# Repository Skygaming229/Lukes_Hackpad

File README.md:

Inspiration
- I wanted to create a macropad that allowed me to work more efficiently. I created a macropad using 6 switches, 1 rp2040, and 2 leds.

Challenges
- Believe it or not, this was my first time using Fusion 360 and KICad! I'm pretty proud of the final product. I had the most truble importing the PCB File into Fusion.

Specifications
BOM:

- 6x Cherry MX Switches
- 2x SK6812 MINI Leds
- 1x XIAO RP2040
- 4x Blank DSA Keycaps
- 4x M3x16 Bolt
- 4x M3 Heatset

Others:

- KMK Firmware
- Heckerpad_luke_case.stl
- Top_Heckpad_Luke.stl

Schematic            |  PCB         |   Case
:-------------------------:|:-------------------------:|:------------------------------:
    |    |

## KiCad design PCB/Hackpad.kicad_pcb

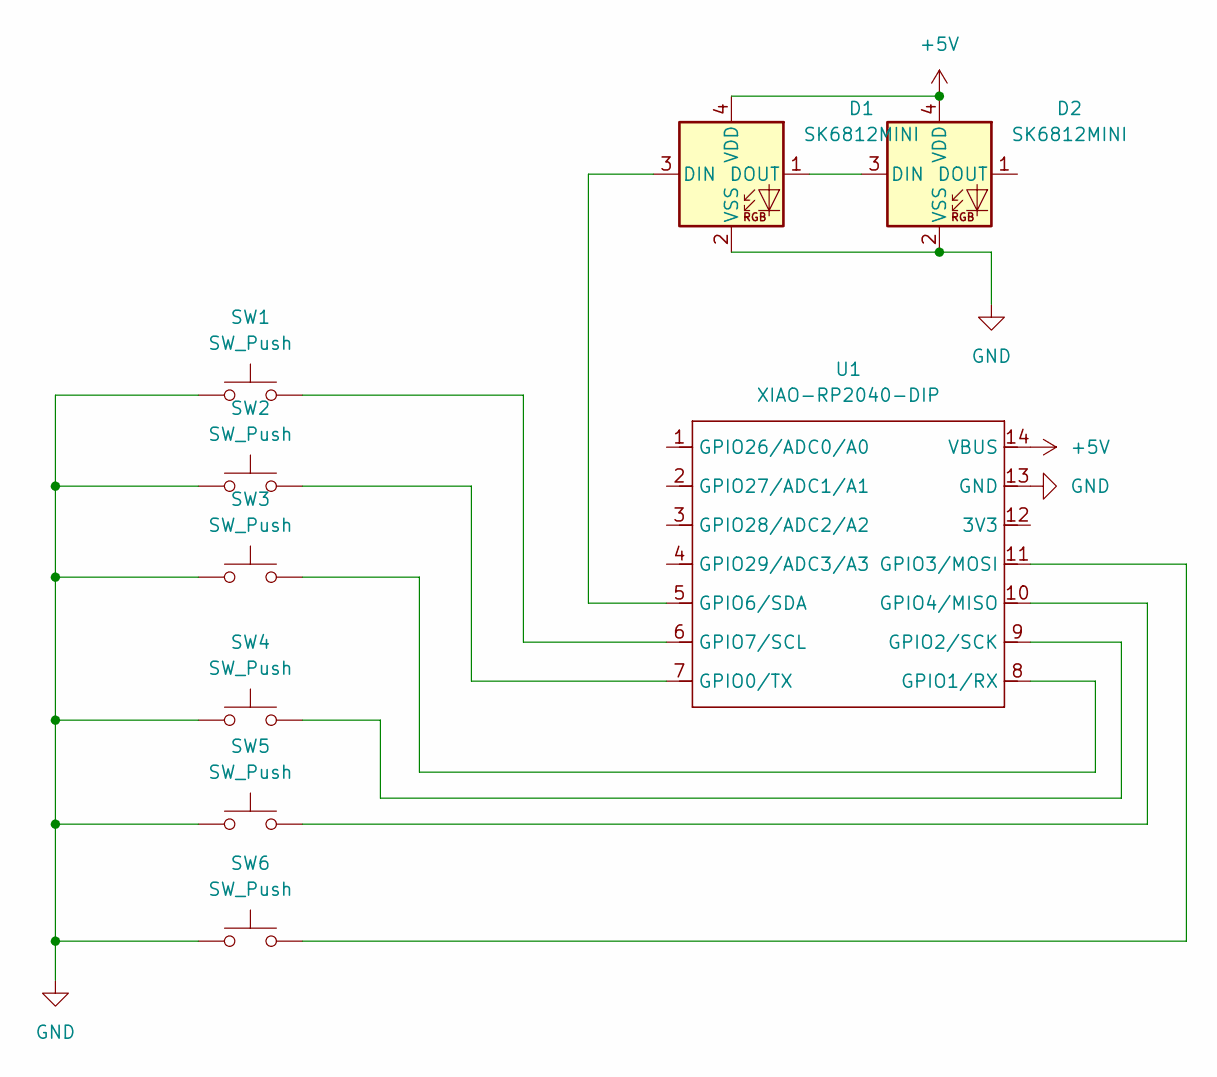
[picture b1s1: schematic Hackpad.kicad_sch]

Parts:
D1, D2: SK6812MINI; LED_SK6812MINI_PLCC4_3.5x3.5mm_P1.75mm
SW1, SW2, SW3, SW4, SW5, SW6: SW_Push; SW_Cherry_MX_1.00u_PCB
U1: XIAO-RP2040-DIP

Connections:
+5V: D1.4 (VDD), D2.4 (VDD), U1.14 (VBUS)
GND: D1.2 (VSS), D2.2 (VSS), SW1.1, SW2.1, SW3.1, SW4.1, SW5.1, SW6.1, U1.13 (GND)
unnamed: D1.3 (DIN), U1.5 (GPIO6/SDA)
unnamed: D1.1 (DOUT), D2.3 (DIN)
unnamed: SW2.2, U1.7 (GPIO0/TX)
unnamed: SW3.2, U1.8 (GPIO1/RX)
unnamed: SW4.2, U1.9 (GPIO2/SCK)
unnamed: SW6.2, U1.11 (GPIO3/MOSI)
unnamed: SW5.2, U1.10 (GPIO4/MISO)
unnamed: SW1.2, U1.6 (GPIO7/SCL)

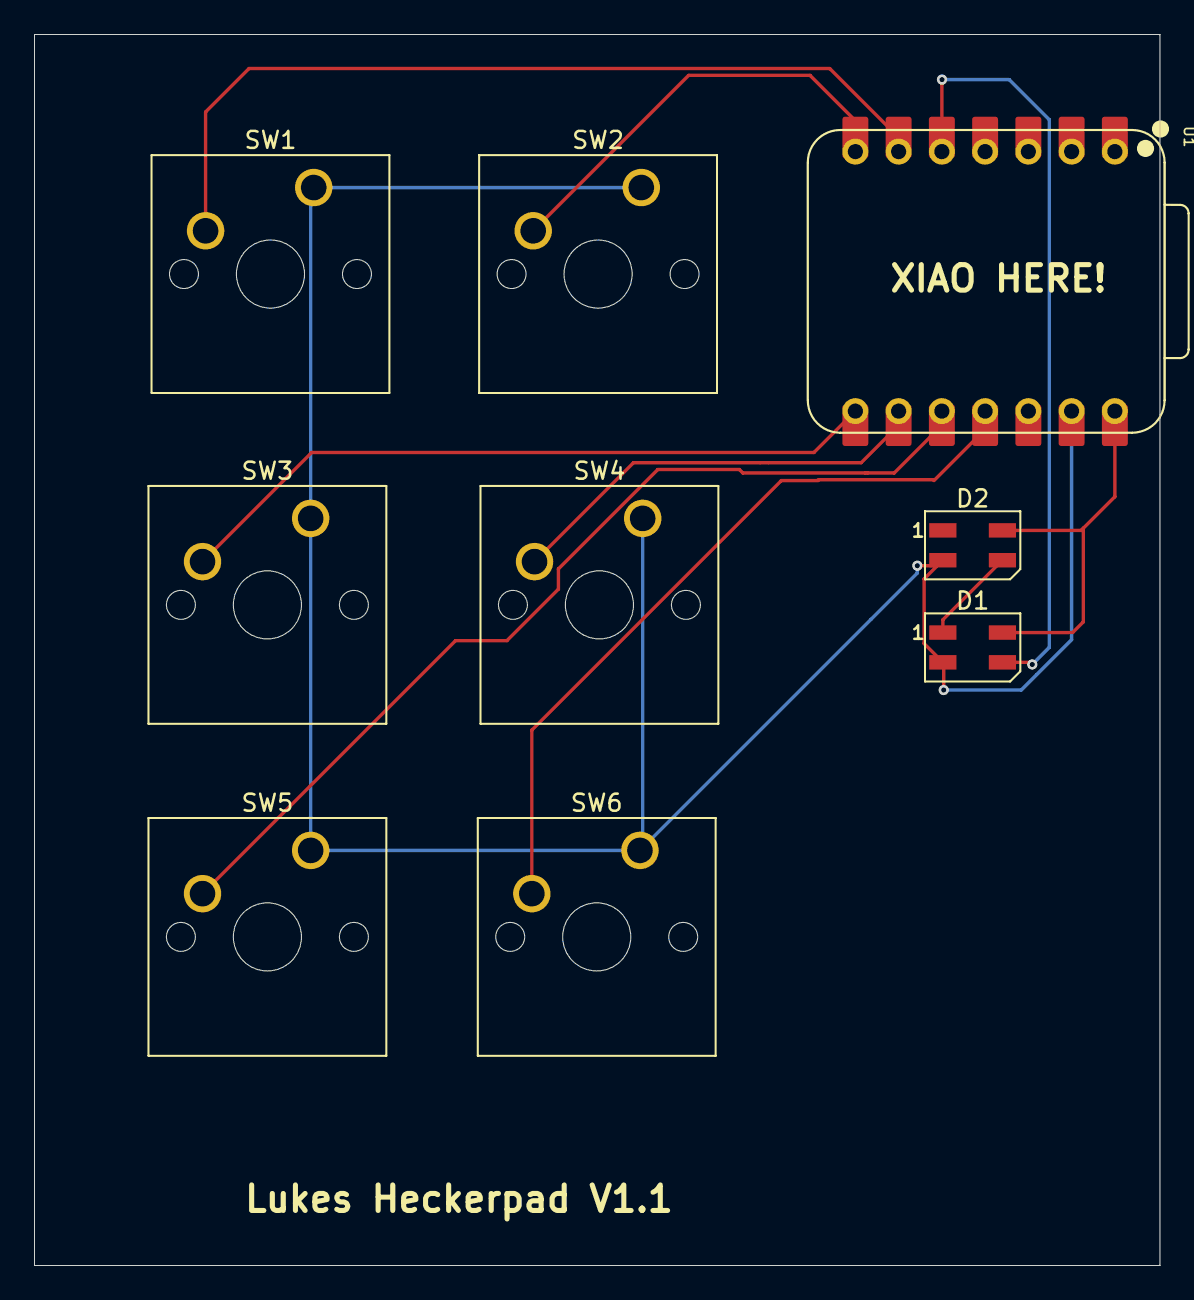
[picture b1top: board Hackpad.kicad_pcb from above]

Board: 2 copper layers, 66.1 x 72.3 mm, 9 parts (0 on the bottom side), 10 nets.

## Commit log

2025-12-04 Added 2 Files
2025-12-04 PCB Files
2025-12-05 Add project details to README.md
    Added detailed project information including inspiration, challenges, specifications, and images.
2025-12-06 KMK erstellen
2025-12-06 Modify pin assignments and add macro functionality
    Updated pin configuration and added macro definition.
2025-12-06 Reorganize project files into CAD and PCB directories
    Moved STL and KiCad files into dedicated CAD and PCB folders for better project structure. Added new KiCad project-related files and a backup ZIP. No changes to file contents.
2025-12-07 Rename KMK.py to main.py
2025-12-07 Add initial Hackpad schematic, code, and README
    Added Hackpad.kicad_sch for the hardware schematic, main.py for the main Python code, and README.md for project documentation. This sets up the initial structure for the Hackpad project including har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
2025-12-07 Rename main.py and update hardware files
    Renamed main.py to Firmware/main.py for better organization. Deleted Hackpad.kicad_sch schematic and added PCB/Hackpad_PCB.zip, likely reflecting updated hardware design files.
2025-12-08 main.py löschen
2025-12-08 main.py aktualisieren
2025-12-08 Hackpad.kicad_sch löschen
2026-01-22 Refactor pin definitions and add Alt+F4 macro
    Updated GPIO pin definitions and added Alt+F4 macro.
2026-02-03 chanced
2026-02-03 Add image to README for visual reference
2026-02-03 Add initial journal entries for Hackpad project
